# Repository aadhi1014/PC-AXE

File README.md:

# PC-AXE: PCIe-Based Bitcoin Miner (12x BM1370, 14.4TH/s @ 200W)

**PC-AXE** is a compact, PCIe x4-based, open-hardware Bitcoin miner designed to plug directly into desktop computers. Inspired by [Bitaxe](https://github.com/skot/bitaxe), Bitcrane, and professional mining cards, PC-AXE uses twelve BM1370 ASIC chips and a 6-phase high-efficiency buck converter to deliver up to **14.4TH/s** of hashrate at just **200W** power draw.

**Note:** PC-AXE is a **work in progress**. Hardware files are being finalized, and firmware development is ongoing. Community contributions and testing feedback are welcome.

---

*Top side of the PC-AXE board*

*Bottom side of the PC-AXE board*

---

## Features

- **Standard PCIe x4 Form Factor**
  - Easily integrates into modern desktop systems
  - Powered via PCIe slot with external power input

- **12 × BM1370 ASIC Chips**
  - Same chips used in Antminer S21
  - Estimated hashrate of ~1.2TH/s per chip

- **6-Phase 180A Buck Converter**
  - High-efficiency power delivery at 1.1V
  - Total power consumption approximately 200W

- **Fully Open-Source Design**
  - Includes KiCad schematics, layout, and source files
  - Planned firmware compatibility with Bitaxe ecosystem

- **UART Debug Interface**
  - Communicates via USB-to-UART bridge (e.g. FT4232H)
  - Supports daisy-chained UART control for ASICs

- **Design Inspiration**
  - Derived from Bitaxe (compact solo miner)
  - Influenced by Bitcrane

---

## Getting Started

### Build Instructions

1. Open the project in KiCad 7 or newer
2. Review the schematic and PCB layout
3. Export Gerber files and order the PCB from your preferred manufacturer
4. Assemble the board using the BOM (to be published)
5. Flash control firmware (currently in development)

### UART Connection

Connect an FTDI FT4232H or equivalent USB-to-UART adapter to the debug header. A single UART channel can control all 12 ASICs.

---

## Important License Notice  
This project was relicensed under the **TAPR Open Hardware License – Non-Commercial (OHL-NC)** on **July 11, 2025**.  
All clones and forks made **after this date** are subject to **non-commercial use only**.  

**Commercial use, manufacturing, or distribution of this work is strictly prohibited without explicit written permission from the copyright holder.**  

If you cloned this repository *before July 11, 2025*, please contact the author for updated licensing terms.

---

## License

This hardware design is licensed under the TAPR Open Hardware License – Non-Commercial (OHL-NC).  
You are free to use, modify, and distribute for **non-commercial purposes**.  

**Commercial use requires explicit written permission from the copyright holder.**  
See the [LICENSE](LICENSE) file for details.

---

## Acknowledgments

This project draws inspiration and technical insight from several open-source mining hardware efforts:

- [Bitaxe](https://github.com/skot/bitaxe) – foundational open hardware Bitcoin miner  
- [NerdAxe](https://github.com/BitMaker-hub/NerdAxe) – compact ESP32-based BM1370 miner 
- [NerdOCTAXE-Gamma](https://github.com/5toliv/NerdOCTAXE-Gamma) – 8‑ASIC miner derived from NerdQaxe 
- [NerdEKO‑Gamma](https://github.com/phil31/NerdEKO-Gamma) – ESP32-based miner reference design   
- [Bitcrane](https://bitcointalk.org/index.php?topic=951507.0) – USB antminer control board  design

We thank these creators for their contributions to the open-source mining community.
---

## Contact / Collaboration

If you are a developer, hardware enthusiast, or miner interested in contributing to this open hardware project, feel free to open issues or pull requests. Community collaboration is welcome.

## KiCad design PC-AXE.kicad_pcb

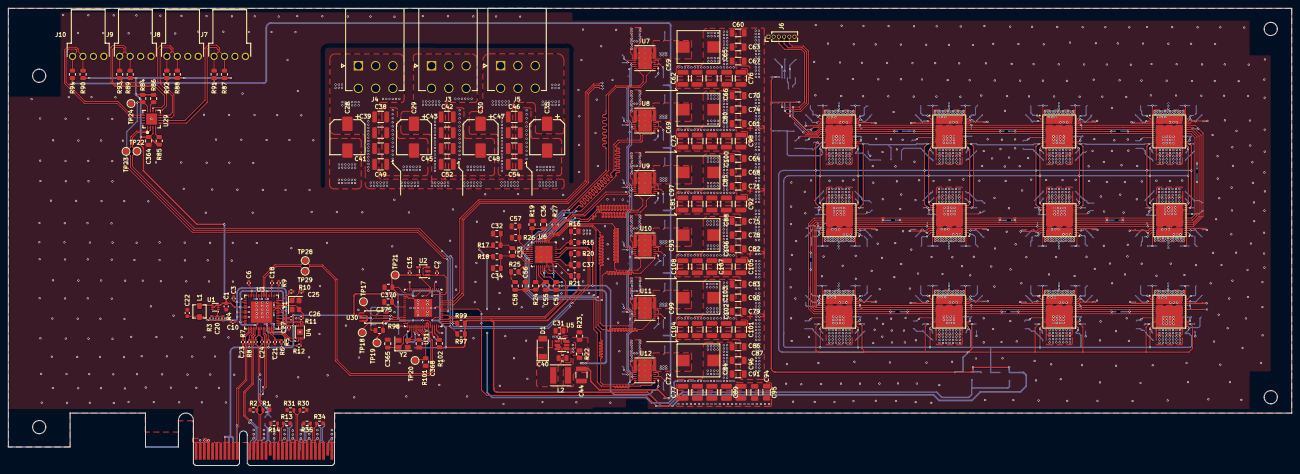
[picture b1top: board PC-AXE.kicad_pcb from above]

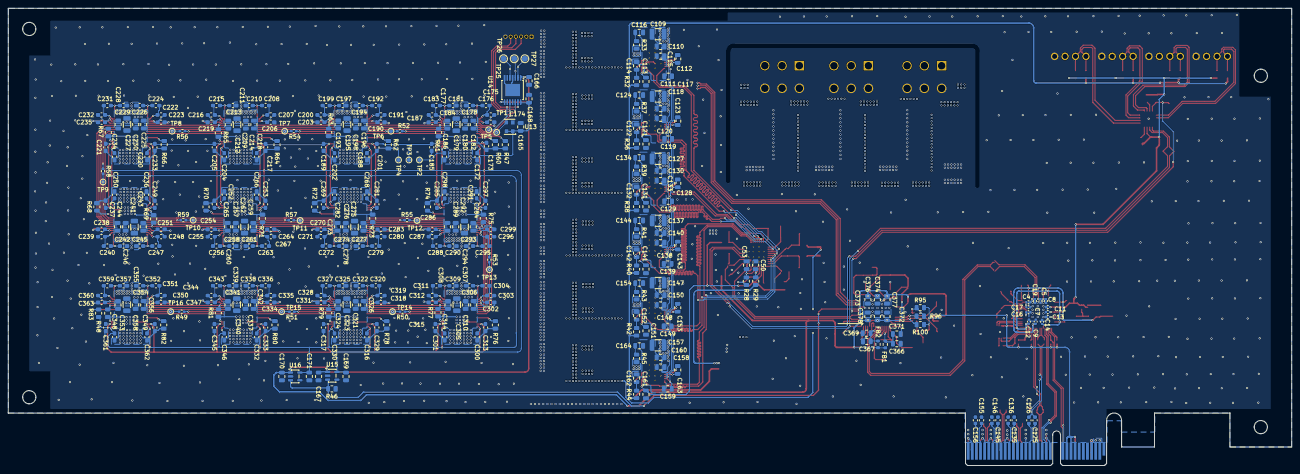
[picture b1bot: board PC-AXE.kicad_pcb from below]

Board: 6 copper layers, 312.0 x 111.2 mm, 565 parts (359 on the bottom side), 297 nets.

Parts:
C1: 10uF; C_0603_1608Metric
C2, C15: 10uF; C_0402_1005Metric
C3, C4, C5, C6, C7, C8, C9, C10, C11, C12, C13, C14, C16, C17, C18, C19, C23, C24, C27: 100nF; C_0402_1005Metric
C20: 10pF; C_0402_1005Metric
C21: 1uF; C_0402_1005Metric
C22: 22uF; C_0603_1608Metric
C25, C26: 18pF; C_0402_1005Metric
C28, C29, C30, C35: 470µ/25V; CP_Elec_8x10
C31, C177, C193, C209, C225, C241, C257, C273, C289, C305, C321, C337, C353: 10µF/25V; C_0805_2012Metric
C32, C34: 22pF; C_0805_2012Metric
C33: 100pF; C_0805_2012Metric
C36, C37, C58, C111, C116, C119, C124, C129, C134, C139, C144, C149, C154, C159, C164: 1nF; C_0805_2012Metric
C38, C39, C41, C42, C43, C44, C45, C46, C47, C48, C49, C52, C54, C109, C117, C127, C137, C147, C157: 22µ/25V; C_1210_3225Metric
C40: 10nF; C_0805_2012Metric
C50: 4.7µF/16V; C_0805_2012Metric
C51, C53, C110, C118, C128, C138, C148, C158, C169, C171, C180, C196, C212, C228, C244, C260, C276, C292, C308, C324, C340, C356: 1µF/25V; C_0805_2012Metric
C55: 330nF; C_0805_2012Metric
C56: 12pF; C_0805_2012Metric
C57: 2.2nF; C_0805_2012Metric
C59, C62, C65, C66, C69, C72, C73, C76, C77, C80, C81, C84, C85, C88, C89, C92, C93, C96, C97, C98, C99, C100, C101, C102, C103, C104, C105, C106, C107, C108: 330µF/4V; C_1210_3225Metric
C60, C61, C63, C64, C67, C68, C70, C71, C74, C75, C78, C79, C82, C83, C86, C87, C90, C91, C94, C95, C179, C195, C211, C227, C243, C259, C275, C291, C307, C323, C339, C355: 100µ/6.3V; C_1206_3216Metric
C112, C113, C115, C120, C121, C123, C130, C131, C133, C140, C141, C143, C150, C151, C153, C160, C161, C163, C165, C166, C167, C168, C170, C182, C198, C214, C230, C246, C262, C278, C294, C310, C326, C342, C358: 100nF; C_0805_2012Metric
C114, C122, C132, C142, C152, C162: 2.2µF/16V; C_0805_2012Metric
C125, C126, C135, C136, C145, C146, C155, C156: 100n; C_0603_1608Metric
C172, C173, C174, C175, C176, C178, C181, C183, C184, C185, C186, C187, C188, C189, C190, C191, C192, C194, C197, C199, C200, C201, C202, C203, C204, C205, C206, C207, C208, C210, C213, C215, C216, C217, C218, C219, C220, C221, C222, C223, C224, C226, C229, C231, C232, C233, C234, C235, C236, C237, C238, C239, C240, C242, C245, C247, C248, C249, C250, C251, C252, C253, C254, C255, C256, C258, C261, C263, C264, C265, C266, C267, C268, C269, C270, C271, C272, C274, C277, C279, C280, C281, C282, C283, C284, C285, C286, C287, C288, C290, C293, C295, C296, C297, C298, C299, C300, C301, C302, C303, C304, C306, C309, C311, C312, C313, C314, C315, C316, C317, C318, C319, C320, C322, C325, C327, C328, C329, C330, C331, C332, C333, C334, C335, C336, C338, C341, C343, C344, C345, C346, C347, C348, C349, C350, C351, C352, C354, C357, C359, C360, C361, C362, C363: 1µF/6.3V; C_0603_1608Metric_Pad1.08x0.95mm_HandSolder
C364, C369, C371, C372, C373, C374, C375, C376, C377, C378: 0.1uF; C_0805_2012Metric
C365, C368: 27pf; C_0805_2012Metric
C366, C367: 4.7uF; C_0805_2012Metric
C370: 3.3uF; C_0805_2012Metric
D1: PMEG4030EP,115; D_SOD-128
FB1, FB2: FerriteBead_Small; R_0603_1608Metric
J1: PCIexpress_bracket; PCIexpress_bracket_full
J2: PCIexpress_x4
J3, J4, J5: 353180620; MOLEX_353180620
J6: Conn_01x06; PinHeader_1x06_P1.27mm_Vertical
J7, J8, J9, J10: 61900411021; CONN-TH_4P-P2.54_HCTL_HC-2510-4AW
L1: 1uH; L_Vishay_IHLP-1212
L2: 4.7µH; L_Taiyo-Yuden_NR-50xx
L3, L4, L5, L6, L7, L8: 220nH; IFLR-4031GC-01-8x10
NT1, NT2: NetTie_2; NetTie-2_SMD_Pad0.5mm
R1, R2, R13, R14, R30, R31, R34, R35: 49.9; R_0603_1608Metric
R3: 75K; R_0402_1005Metric
R4: 100K; R_0402_1005Metric
R5, R6, R8, R12: 10K; R_0402_1005Metric
R7: DNP; R_0402_1005Metric
R9: 4.7K; R_0402_1005Metric
R10: 6.04K; R_0402_1005Metric
R11: 15K; R_0402_1005Metric
R15, R23: 16.5K; R_0805_2012Metric
R16: 24.3K; R_0805_2012Metric
R17, R18: 51 0.5%; R_0805_2012Metric
R19: 121K; R_0805_2012Metric
R20, R21, R46, R47, R48: 10K; R_0805_2012Metric
R22: 86.6K; R_0805_2012Metric
R24: 2.55K; R_0805_2012Metric
R25: 8.06K; R_0805_2012Metric
R26: 33.2K; R_0805_2012Metric
R27: 100K; R_0805_2012Metric
R28, R29: 2.2R; R_0805_2012Metric
R32, R33, R36, R37, R38, R39, R40, R41, R42, R43, R44, R45: 1R; R_0805_2012Metric
R49, R50, R51, R52, R53, R54, R55, R56, R57, R58, R59: 33R; R_0402_1005Metric_Pad0.72x0.64mm_HandSolder
R60, R62, R64, R66, R68, R70, R72, R74, R76, R78, R80, R82: 1K; R_0805_2012Metric
R61, R63, R65, R67, R69, R71, R73, R75, R77, R79, R81, R83: 2K; R_0805_2012Metric
R84, R97, R99: 4.7k; R_0805_2012Metric
R85: 33k; R_0805_2012Metric
R86: 22k; R_0805_2012Metric
R87, R88, R89, R90: 36k; R_0805_2012Metric
R91, R92, R93, R94, R95, R98, R100: 10k; R_0805_2012Metric
R96: 2.2k; R_0805_2012Metric
R101: 12k; R_0805_2012Metric
R102: 1k; R_0805_2012Metric
TP1, TP2, TP3, TP4, TP5, TP6, TP7, TP8, TP9, TP10, TP11, TP12, TP13, TP14, TP15, TP16: TestPoint; TestPoint_Pad_D1.0mm
TP17, TP18, TP19, TP20, TP21, TP22, TP23, TP24, TP25, TP26, TP27, TP28, TP29: TestPoint; TestPoint_Pad_D1.5mm
U1: TLV62568ADRLR; SOT-563
U2: AP2204K-1.8; SOT-23-5
U3: VL805; QFN-68-1EP_8x8mm_P0.4mm_EP5.2x5.2mm
U4: W25Q32JVZP; DFN-8-1EP_3x2mm_P0.5mm_EP1.36x1.46mm
U5: AP3211; SOT-23-6
U6: TPS53667RTAR; IC_TPS53667RTAR
U7, U8, U9, U10, U11, U12: CSD95472Q5MC; IC_CSD95490Q5MC
U13: 25MHz; Oscillator_SMD_EuroQuartz_XO32-4Pin_3.2x2.5mm
U14: TXU0304PW; TSSOP-14-1EP_4.4x5mm_P0.65mm
U15: MCP1824T-0802E; SOT-23-5
U16: MCP1824T-1202E; SOT-23-5
U17, U18, U19, U20, U21, U22, U23, U24, U25, U26, U27, U28: BM1370_mode1; BM1370
U29: EMC2305; QFN16_4x4MC_MCH
U30: M93C46-WDW6TP; TSSOP-8_L4.4-W3.0-P0.65-LS6.4-BL
U31: FT4232HQ; QFN50P900X900X105-65N
Y1: 25Mhz; Crystal_SMD_3225-4Pin_3.2x2.5mm
Y2: 12MHz; Crystal_SMD_3225-4Pin_3.2x2.5mm

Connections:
+0V8: C169.1, C173.2, C185.2, C189.2, C201.2, C205.2, C217.2, C221.2, C233.2, C237.2, C249.2, C253.2, C265.2, C269.2, C281.2, C285.2, C297.2, C301.2, C313.2, C317.2, C329.2, C333.2, C345.2, C349.2, C361.2, TP3.1, U15.5 (VOUT), U17.14 (VDDIO_08_0), U17.17 (VDDIO_08_1), U18.14 (VDDIO_08_0), U18.17 (VDDIO_08_1), U19.14 (VDDIO_08_0), U19.17 (VDDIO_08_1), U20.14 (VDDIO_08_0), U20.17 (VDDIO_08_1), U21.14 (VDDIO_08_0), U21.17 (VDDIO_08_1), U22.14 (VDDIO_08_0), U22.17 (VDDIO_08_1), U23.14 (VDDIO_08_0), U23.17 (VDDIO_08_1), U24.14 (VDDIO_08_0), U24.17 (VDDIO_08_1), U25.14 (VDDIO_08_0), U25.17 (VDDIO_08_1), U26.14 (VDDIO_08_0), U26.17 (VDDIO_08_1), U27.14 (VDDIO_08_0), U27.17 (VDDIO_08_1), U28.14 (VDDIO_08_0), U28.17 (VDDIO_08_1)
+1V1: C3.2, C5.2, C7.2, C9.2, C11.2, C13.2, C16.2, C18.2, C20.1, C22.1, L1.2, R3.1, U3.3 (VCCA10SSRX34), U3.9 (VDD), U3.12 (VCCA10SSRX34), U3.29 (VDD), U3.45 (VDD), U3.54 (VCCA10SSRX12), U3.60 (VDD), U3.63 (VCCA10SSRX12)
+1V2: C165.1, C168.1, C171.1, C172.1, C186.1, C188.1, C202.1, C204.1, C218.1, C220.1, C234.1, C236.1, C250.1, C252.1, C266.1, C268.1, C282.1, C284.1, C298.1, C300.1, C314.1, C316.1, C330.1, C332.1, C346.1, C348.1, C362.1, R48.2, TP2.1, U13.1 (Standby), U13.4 (VDD), U14.14 (VCCB), U16.5 (VOUT), U17.15 (VDDIO_12_0), U17.16 (VDDIO_12_1), U18.15 (VDDIO_12_0), U18.16 (VDDIO_12_1), U19.15 (VDDIO_12_0), U19.16 (VDDIO_12_1), U20.15 (VDDIO_12_0), U20.16 (VDDIO_12_1), U21.15 (VDDIO_12_0), U21.16 (VDDIO_12_1), U22.15 (VDDIO_12_0), U22.16 (VDDIO_12_1), U23.15 (VDDIO_12_0), U23.16 (VDDIO_12_1), U24.15 (VDDIO_12_0), U24.16 (VDDIO_12_1), U25.15 (VDDIO_12_0), U25.16 (VDDIO_12_1), U26.15 (VDDIO_12_0), U26.16 (VDDIO_12_1), U27.15 (VDDIO_12_0), U27.16 (VDDIO_12_1), U28.15 (VDDIO_12_0), U28.16 (VDDIO_12_1)
+1V8: C15.1, C370.1, C372.1, C373.1, C374.1, TP21.1, U2.5 (VOUT), U31.12 (VCORE), U31.37 (VCORE), U31.49 (VREGOUT), U31.64 (VCORE)
+3V3: C1.2, C2.1, C4.2, C6.2, C8.2, C10.2, C12.2, C14.2, C17.2, C19.2, C27.2, C166.1, C167.1, C170.1, C364.1, C375.1, C376.1, C377.1, C378.1, FB1.1, FB2.1, J2.A9 (+3.3V), J2.A10 (+3.3V), J2.B8 (+3.3V), R5.2, R6.2, R7.2, R8.2, R11.2, R12.1, R21.1, R84.2, R85.2, R86.2, R87.1, R88.1, R89.1, R90.1, R95.2, R97.2, R98.2, R99.2, R100.2, R102.1, U1.3 (VIN), U1.5 (EN), U2.1 (VIN), U2.3 (EN), U3.6 (VCCA33SS34), U3.15 (VCCA33SS34), U3.23 (VCCA33PEX), U3.32 (VSUS33), U3.46 (VSUS33), U3.49 (VCCA33SSM), U3.57 (VCCA33SS12), U3.66 (VCCA33SS12), U4.7 (IO3), U4.8 (VCC), U14.1 (VCCA), U14.8 (OE), U15.1 (VIN), U16.1 (VIN), U29.3 (VDD), U30.6 (ORG), U30.8 (VCC), U31.20 (VCCIO), U31.31 (VCCIO), U31.42 (VCCIO), U31.50 (VREGIN), U31.56 (VCCIO)
+5V_STDBY: C44.1, L2.2, R22.1, R29.1, R32.1, R36.1, R38.1, R40.1, R42.1, R44.1, R91.2, R92.2, R93.2, R94.2
+12V: C28.1, C29.1, C30.1, C31.1, C35.1, C38.1, C39.1, C41.1, C42.1, C43.1, C45.1, C46.1, C47.1, C48.1, C49.1, C52.1, C54.1, C109.1, C110.1, C112.1, C117.1, C118.1, C120.1, C127.1, C128.1, C130.1, C137.1, C138.1, C140.1, C147.1, C148.1, C150.1, C157.1, C158.1, C160.1, J2.A2 (+12V), J2.A3 (+12V), J2.B1 (+12V), J2.B2 (+12V), J2.B3 (+12V), J3.1, J3.2, J3.3, J4.1, J4.2, J4.3, J5.1, J5.2, J5.3, J7.2, J8.2, J9.2, J10.2, R28.1, U5.4 (EN), U5.5 (IN), U7.7 (VIN), U8.7 (VIN), U9.7 (VIN), U10.7 (VIN), U11.7 (VIN), U12.7 (VIN)
+VREF: C55.1, C56.2, C58.2, C113.1, C121.1, C131.1, C141.1, C151.1, C161.1, R15.2, R24.2, U6.13 (VREF), U7.2 (REFIN), U8.2 (REFIN), U9.2 (REFIN), U10.2 (REFIN), U11.2 (REFIN), U12.2 (REFIN)
/BM1370_chain/BM1370-1/BI: R47.2, U17.9 (BI)
/BM1370_chain/BM1370-1/BO: U17.22 (BO), U18.9 (BI)
/BM1370_chain/BM1370-1/CLKI: TP5.1, U13.3 (Out), U17.8 (CLKI)
/BM1370_chain/BM1370-1/CLKO: R52.1, U17.23 (CLKO)
/BM1370_chain/BM1370-1/CO: U17.25 (CO), U18.6 (CI)
/BM1370_chain/BM1370-1/NRSTO: R61.2, U17.26 (NRSTO), U18.5 (NRSTI)
/BM1370_chain/BM1370-1/RI: U17.24 (RI), U18.7 (RO)
/BM1370_chain/BM1370-2/BO: U18.22 (BO), U19.9 (BI)
/BM1370_chain/BM1370-2/CLKI: R52.2, TP6.1, U18.8 (CLKI)
/BM1370_chain/BM1370-2/CLKO: R54.1, U18.23 (CLKO)
/BM1370_chain/BM1370-2/CO: U18.25 (CO), U19.6 (CI)
/BM1370_chain/BM1370-2/NRSTO: R63.2, U18.26 (NRSTO), U19.5 (NRSTI)
/BM1370_chain/BM1370-2/RI: U18.24 (RI), U19.7 (RO)
/BM1370_chain/BM1370-3/BO: U19.22 (BO), U20.9 (BI)
/BM1370_chain/BM1370-3/CLKI: R54.2, TP7.1, U19.8 (CLKI)
/BM1370_chain/BM1370-3/CLKO: R56.1, U19.23 (CLKO)
/BM1370_chain/BM1370-3/CO: U19.25 (CO), U20.6 (CI)
/BM1370_chain/BM1370-3/NRSTO: R65.2, U19.26 (NRSTO), U20.5 (NRSTI)
/BM1370_chain/BM1370-3/RI: U19.24 (RI), U20.7 (RO)
/BM1370_chain/BM1370-4/BO: U20.22 (BO), U21.9 (BI)
/BM1370_chain/BM1370-4/CLKI: R56.2, TP8.1, U20.8 (CLKI)
/BM1370_chain/BM1370-4/CLKO: R58.1, U20.23 (CLKO)
/BM1370_chain/BM1370-4/CO: U20.25 (CO), U21.6 (CI)
/BM1370_chain/BM1370-4/NRSTO: R67.2, U20.26 (NRSTO), U21.5 (NRSTI)
/BM1370_chain/BM1370-4/RI: U20.24 (RI), U21.7 (RO)
/BM1370_chain/BM1370-5/BO: U21.22 (BO), U22.9 (BI)
/BM1370_chain/BM1370-5/CLKI: R58.2, TP9.1, U21.8 (CLKI)
/BM1370_chain/BM1370-5/CLKO: R59.1, U21.23 (CLKO)
/BM1370_chain/BM1370-5/CO: U21.25 (CO), U22.6 (CI)
/BM1370_chain/BM1370-5/NRSTO: R69.2, U21.26 (NRSTO), U22.5 (NRSTI)
/BM1370_chain/BM1370-5/RI: U21.24 (RI), U22.7 (RO)
/BM1370_chain/BM1370-6/BO: U22.22 (BO), U23.9 (BI)
/BM1370_chain/BM1370-6/CLKI: R59.2, TP10.1, U22.8 (CLKI)
/BM1370_chain/BM1370-6/CLKO: R57.1, U22.23 (CLKO)
/BM1370_chain/BM1370-6/CO: U22.25 (CO), U23.6 (CI)
/BM1370_chain/BM1370-6/NRSTO: R71.2, U22.26 (NRSTO), U23.5 (NRSTI)
/BM1370_chain/BM1370-6/RI: U22.24 (RI), U23.7 (RO)
/BM1370_chain/BM1370-7/BO: U23.22 (BO), U24.9 (BI)
/BM1370_chain/BM1370-7/CLKI: R57.2, TP11.1, U23.8 (CLKI)
/BM1370_chain/BM1370-7/CLKO: R55.1, U23.23 (CLKO)
/BM1370_chain/BM1370-7/CO: U23.25 (CO), U24.6 (CI)
/BM1370_chain/BM1370-7/NRSTO: R73.2, U23.26 (NRSTO), U24.5 (NRSTI)
/BM1370_chain/BM1370-7/RI: U23.24 (RI), U24.7 (RO)
/BM1370_chain/BM1370-8/BO: U24.22 (BO), U25.9 (BI)
/BM1370_chain/BM1370-8/CLKI: R55.2, TP12.1, U24.8 (CLKI)
/BM1370_chain/BM1370-8/CLKO: R53.1, U24.23 (CLKO)
/BM1370_chain/BM1370-8/CO: U24.25 (CO), U25.6 (CI)
/BM1370_chain/BM1370-8/NRSTO: R75.2, U24.26 (NRSTO), U25.5 (NRSTI)
/BM1370_chain/BM1370-8/RI: U24.24 (RI), U25.7 (RO)
/BM1370_chain/BM1370-9/CLKI: R53.2, TP13.1, U25.8 (CLKI)
/BM1370_chain/BM1370-9/CLKO: R50.1, U25.23 (CLKO)
/BM1370_chain/BM1370-10/BI: U25.22 (BO), U26.9 (BI)
/BM1370_chain/BM1370-10/BO: U26.22 (BO), U27.9 (BI)
/BM1370_chain/BM1370-10/CI: U25.25 (CO), U26.6 (CI)
/BM1370_chain/BM1370-10/CLKI: R50.2, TP14.1, U26.8 (CLKI)
/BM1370_chain/BM1370-10/CLKO: R51.1, U26.23 (CLKO)
/BM1370_chain/BM1370-10/CO: U26.25 (CO), U27.6 (CI)
/BM1370_chain/BM1370-10/NRSTI: R77.2, U25.26 (NRSTO), U26.5 (NRSTI)
/BM1370_chain/BM1370-10/NRSTO: R79.2, U26.26 (NRSTO), U27.5 (NRSTI)
/BM1370_chain/BM1370-10/RI: U26.24 (RI), U27.7 (RO)
/BM1370_chain/BM1370-10/RO: U25.24 (RI), U26.7 (RO)
/BM1370_chain/BM1370-11/BO: U27.22 (BO), U28.9 (BI)
/BM1370_chain/BM1370-11/CLKI: R51.2, TP15.1, U27.8 (CLKI)
/BM1370_chain/BM1370-11/CLKO: R49.1, U27.23 (CLKO)
/BM1370_chain/BM1370-11/CO: U27.25 (CO), U28.6 (CI)
/BM1370_chain/BM1370-11/NRSTO: R81.2, U27.26 (NRSTO), U28.5 (NRSTI)
/BM1370_chain/BM1370-11/RI: U27.24 (RI), U28.7 (RO)
/BM1370_chain/BM1370-12/CLKI: R49.2, TP16.1, U28.8 (CLKI)
/BM1370_chain/BM1370-12/NRSTO: R83.2, U28.26 (NRSTO)
/BM1370_chain/BM1370-12/RI: R48.1, U28.24 (RI)
/BM1370_chain/CI: J6.4, U14.12 (B2Y), U17.6 (CI)
/BM1370_chain/RO: J6.5, U14.10 (B4), U17.7 (RO)
/BM1370_chain/RST_N: J6.3, TP1.1, U14.13 (B1Y), U17.5 (NRSTI)
/DN: TP28.1, U3.59 (USB2D1-), U31.7 (DM)
/DP: TP29.1, U3.58 (USB2D1+), U31.8 (DP)
/FAN/PWM1: J7.4, R91.1, U29.5 (PWM1)
/FAN/PWM2: J8.4, R92.1, U29.7 (PWM2)
/FAN/PWM3: J9.4, R93.1, U29.9 (PWM3)
/FAN/PWM4: J10.4, R94.1, U29.13 (PWM4)
/FAN/TACH1: J7.3, R87.2, U29.6 (TACH1)
/FAN/TACH2: J8.3, R88.2, U29.8 (TACH2)
/FAN/TACH3: J9.3, R89.2, U29.10 (TACH3)
/FAN/TACH4: J10.3, R90.2, U29.14 (TACH4)
/FAN_ALERT: R84.1, TP24.1, U29.12 (~ALERT), U31.23 (ADBUS6)
/LDO_EN: R46.1, U15.3 (EN), U16.3 (EN), U31.24 (ADBUS7)
/PCIexpress_connector/_PER0_N: C126.1, J2.A17 (PERn0)
/PCIexpress_connector/_PER0_P: C125.2, J2.A16 (PERp0)
/PCIexpress_connector/_PER1_N: C136.1, J2.A22 (PERn1)
/PCIexpress_connector/_PER1_P: C135.2, J2.A21 (PERp1)
/PCIexpress_connector/_PER2_N: C146.1, J2.A26 (PERn2)
/PCIexpress_connector/_PER2_P: C145.2, J2.A25 (PERp2)
/PCIexpress_connector/_PER3_N: C156.1, J2.A30 (PERn3)
/PCIexpress_connector/_PER3_P: C155.2, J2.A29 (PERp3)
/PER0_N: C23.1, C126.2
/PER0_P: C24.1, C125.1
/PET0_N: J2.B15 (PETn0), R1.1, U3.27 (PE_RXP)
/PET0_P: J2.B14 (PETp0), R2.1, U3.28 (PE_RXN)
/PET1_N: J2.B20 (PETn1), R13.1
/PET1_P: J2.B19 (PETp1), R14.1
/PET2_N: J2.B24 (PETn2), R30.1
/PET2_P: J2.B23 (PETp2), R31.1
/PET3_N: J2.B28 (PETn3), R34.1
/PET3_P: J2.B27 (PETp3), R35.1
/POWER/FCCM: R27.2, U6.39 (~SKIP-NVM), U7.10 (FCCM), U8.10 (FCCM), U9.10 (FCCM), U10.10 (FCCM), U11.10 (FCCM), U12.10 (FCCM)
/POWER/TPS_CSP1: U6.3 (CSP1), U9.1 (IOUT)
/POWER/TPS_CSP2: U6.4 (CSP2), U7.1 (IOUT)
/POWER/TPS_CSP3: U6.5 (CSP3), U8.1 (IOUT)
/POWER/TPS_CSP4: U6.6 (CSP4), U10.1 (IOUT)
/POWER/TPS_CSP5: U6.7 (CSP5), U11.1 (IOUT)
/POWER/TPS_CSP6: U6.8 (CSP6), U12.1 (IOUT)
/POWER/TPS_PWM1: U6.38 (PWM1), U9.12 (PWM)
/POWER/TPS_PWM2: U6.37 (PWM2), U7.12 (PWM)
/POWER/TPS_PWM3: U6.36 (PWM3), U8.12 (PWM)
/POWER/TPS_PWM4: U6.35 (PWM4), U10.12 (PWM)
/POWER/TPS_PWM5: U6.34 (PWM5), U11.12 (PWM)
/POWER/TPS_PWM6: U6.33 (PWM6), U12.12 (PWM)
/POWER/TSEN: C36.1, C111.1, C119.1, C129.1, C139.1, C149.1, C159.1, R19.2, U6.40 (TSEN), U7.11 (TAO/FAULT), U8.11 (TAO/FAULT), U9.11 (TAO/FAULT), U10.11 (TAO/FAULT), U11.11 (TAO/FAULT), U12.11 (TAO/FAULT)
/POWER/VSENSE+: NT1.2, R17.1
/POWER/VSENSE-: NT2.2, R18.1
/POWER//RESET: R21.2, U6.21 (~RESET)
/REFCLK+: J2.A13 (REFCLK+), U3.21 (PE_CLKP)
/REFCLK-: J2.A14 (REFCLK-), U3.22 (PE_CLKN)
/RESET_N: TP27.1, U14.2 (A1), U31.28 (BDBUS2)
/RXD: TP26.1, U14.5 (A4Y), U31.27 (BDBUS1)
/SCL: R97.1, TP22.1, U6.24 (PMB_CLK), U29.2 (SMCLK), U31.16 (ADBUS0)
/SDA: R99.1, TP23.1, U6.26 (PMB_DIO), U29.1 (SMDATA), U31.17 (ADBUS1), U31.18 (ADBUS2)
/TXD: TP25.1, U14.3 (A2), U31.26 (BDBUS0)
/USB/PCIe_CLK_REQ: R6.1, U3.30 (~PE_CLKREQ)
/USB/SMI: R7.1, U3.18 (~SMI)
/VR_ENABLE: C37.1, R20.1, U6.23 (ENABLE), U31.19 (ADBUS3)
/VR_READY: U6.18 (VR_RDY), U31.21 (ADBUS4)
/~PERST: J2.A11 (~PERST), U3.19 (~PE_RST)
/~WAKE: J2.B11 (~WAKE), R8.1, U3.20 (~PE_WAKE)
GND: C1.1, C2.2, C3.1, C4.1, C5.1, C6.1, C7.1, C8.1, C9.1, C10.1, C11.1, C12.1, C13.1, C14.1, C15.2, C16.1, C17.1, C18.1, C19.1, C21.1, C22.2, C25.1, C26.1, C27.1, C28.2, C29.2, C30.2, C31.2, C32.1, C34.2, C35.2, C36.2, C37.2, C38.2, C39.2, C41.2, C42.2, C43.2, C44.2, C45.2, C46.2, C47.2, C48.2, C49.2, C50.1, C51.2, C52.2, C53.1, C54.2, C55.2, C57.2, C59.2, C60.2, C61.2, C62.2, C63.2, C64.2, C65.2, C66.2, C67.2, C68.2, C69.2, C70.2, C71.2, C72.2, C73.2, C74.2, C75.2, C76.2, C77.2, C78.2, C79.2, C80.2, C81.2, C82.2, C83.2, C84.2, C85.2, C86.2, C87.2, C88.2, C89.2, C90.2, C91.2, C92.2, C93.2, C94.2, C95.2, C96.2, C97.2, C98.2, C99.2, C100.2, C101.2, C102.2, C103.2, C104.2, C105.2, C106.2, C107.2, C108.2, C109.2, C110.2, C111.2, C112.2, C113.2, C114.2, C116.2, C117.2, C118.2, C119.2, C120.2, C121.2, C122.2, C124.2, C127.2, C128.2, C129.2, C130.2, C131.2, C132.2, C134.2, C137.2, C138.2, C139.2, C140.2, C141.2, C142.2, C144.2, C147.2, C148.2, C149.2, C150.2, C151.2, C152.2, C154.2, C157.2, C158.2, C159.2, C160.2, C161.2, C162.2, C164.2, C165.2, C166.2, C167.2, C168.2, C169.2, C170.2, C171.2, C172.2, C173.1, C174.1, C177.2, C179.2, C180.2, C182.2, C185.1, C186.2, C187.2, C188.2, C189.1, C190.1, C193.2, C195.2, C196.2, C198.2, C201.1, C202.2, C203.2, C204.2, C205.1, C206.1, C209.2, C211.2, C212.2, C214.2, C217.1, C218.2, C219.2, C220.2, C221.1, C222.1, C225.2, C227.2, C228.2, C230.2, C233.1, C234.2, C235.2, C236.2, C237.1, C238.1, C241.2, C243.2, C244.2, C246.2, C249.1, C250.2, C251.2, C252.2, C253.1, C254.1, C257.2, C259.2, C260.2, C262.2, C265.1, C266.2, C267.2, C268.2, C269.1, C270.1, C273.2, C275.2, C276.2, C278.2, C281.1, C282.2, C283.2, C284.2, C285.1, C286.1, C289.2, C291.2, C292.2, C294.2, C297.1, C298.2, C299.2, C300.2, C301.1, C302.1, C305.2, C307.2, C308.2, C310.2, C313.1, C314.2, C315.2, C316.2, C317.1, C318.1, C321.2, C323.2, C324.2, C326.2, C329.1, C330.2, C331.2, C332.2, C333.1, C334.1, C337.2, C339.2, C340.2, C342.2, C345.1, C346.2, C347.2, C348.2, C349.1, C350.1, C353.2, C355.2, C356.2, C358.2, C361.1, C362.2, C363.2, C364.2, C365.2, C366.2, C367.2, C368.2, C369.2, C370.2, C371.2, C372.2, C373.2, C374.2, C375.2, C376.2, C377.2, C378.2, D1.2 (A), J2.A4 (GND), J2.A12 (GND), J2.A15 (GND), J2.A18 (GND), J2.A20 (GND), J2.A23 (GND), J2.A24 (GND), J2.A27 (GND), J2.A28 (GND), J2.A31 (GND), J2.B4 (GND), J2.B7 (GND), J2.B13 (GND), J2.B16 (GND), J2.B18 (GND), J2.B21 (GND), J2.B22 (GND), J2.B25 (GND), J2.B26 (GND), J2.B29 (GND), J2.B32 (GND), J3.4, J3.5, J3.6, J4.4, J4.5, J4.6, J5.4, J5.5, J5.6, J6.6, J7.1, J8.1, J9.1, J10.1, NT2.1, R1.2, R2.2, R4.2, R9.1, R10.1, R13.2, R14.2, R16.1, R19.1, R20.2, R23.2, R26.1, R27.1, R30.2, R31.2, R34.2, R35.2, R46.2, R47.1, R60.2, R61.1, R62.2, R63.1, R64.2, R65.1, R66.2, R67.1, R68.2, R69.1, R70.2, R71.1, R72.2, R73.1, R74.2, R75.1, R76.2, R77.1, R78.2, R79.1, R80.2, R81.1, R82.2, R83.1, R101.1, TP4.1, U1.2 (GND), U2.2 (GND), U3.69 (GND), U4.4 (GND), U4.9 (EP), U5.2 (GND), U6.17 (GND_17), U6.20 (GND_20), U6.22 (GND_22), U6.41 (EXP), U7.4 (PGND), U7.13 (PGND), U8.4 (PGND), U8.13 (PGND), U9.4 (PGND), U9.13 (PGND), U10.4 (PGND), U10.13 (PGND), U11.4 (PGND), U11.13 (PGND), U12.4 (PGND), U12.13 (PGND), U13.2 (GND), U14.4 (A3), U14.7 (GND), U14.15 (GND), U15.2 (GND), U16.2 (GND), U17.4 (VSS), U17.13 (PLL_VSS), U17.18 (VSS), U17.27 (VSS), U17.32 (VSS), U18.4 (VSS), U18.13 (PLL_VSS), U18.18 (VSS), U18.27 (VSS), U18.32 (VSS), U19.4 (VSS), U19.13 (PLL_VSS), U19.18 (VSS), U19.27 (VSS), U19.32 (VSS), U20.4 (VSS), U20.13 (PLL_VSS), U20.18 (VSS), U20.27 (VSS), U20.32 (VSS), U21.4 (VSS), U21.13 (PLL_VSS), U21.18 (VSS), U21.27 (VSS), U21.32 (VSS), U22.4 (VSS), U22.13 (PLL_VSS), U22.18 (VSS), U22.27 (VSS), U22.32 (VSS), U23.4 (VSS), U23.13 (PLL_VSS), U23.18 (VSS), U23.27 (VSS), U23.32 (VSS), U24.4 (VSS), U24.13 (PLL_VSS), U24.18 (VSS), U24.27 (VSS), U24.32 (VSS), U25.4 (VSS), U25.13 (PLL_VSS), U25.18 (VSS), U25.27 (VSS), U25.32 (VSS), U26.4 (VSS), U26.13 (PLL_VSS), U26.18 (VSS), U26.27 (VSS), U26.32 (VSS), U27.4 (VSS), U27.13 (PLL_VSS), U27.18 (VSS), U27.27 (VSS), U27.32 (VSS), U28.4 (VSS), U28.13 (PLL_VSS), U28.18 (VSS), U28.27 (VSS), U28.32 (VSS), U29.17 (GND), U30.5 (VSS), U30.7 (DU), U31.1 (GND), U31.5 (GND), U31.10 (AGND), U31.11 (GND), U31.13 (TEST), U31.15 (GND), U31.25 (GND), U31.35 (GND), U31.47 (GND), U31.51 (GND), U31.65 (EPAD), Y1.2, Y1.4, Y2.2 (GND), Y2.4 (GND__1)
unnamed: C58.1, R25.1
unnamed: C116.1, R33.1
unnamed: C124.1, R37.1
unnamed: C134.1, R39.1
unnamed: C144.1, R41.1
unnamed: C154.1, R43.1
unnamed: C164.1, R45.1
unnamed: C40.2, D1.1 (K), L2.1, U5.6 (SW)
unnamed: C20.2, R3.2, R4.1, U1.1 (FB)
unnamed: L1.1, U1.4 (SW)
unnamed: C24.2, U3.25 (PE_TXN)
unnamed: C23.2, U3.24 (PE_TXP)
unnamed: U3.35 (SPI_CLK), U4.6 (CLK)
unnamed: U3.34 (SPI_CS), U4.1 (~CS)
unnamed: U3.36 (SPI_DI), U4.5 (DI(IO0))
unnamed: U3.33 (SPI_DO), U4.2 (DO(IO1))
unnamed: R10.2, U3.50 (SSREXT)
unnamed: R9.2, U3.51 (TESTEN)
unnamed: C26.2, U3.47 (XI), Y1.3
unnamed: C25.2, U3.48 (XO), Y1.1
unnamed: C21.2, R5.1, U3.31 (~PONRST)
unnamed: R11.1, U3.37 (~USBHOC4), U3.39 (~USBHOC3), U3.41 (~USBHOC2), U3.43 (~USBHOC1)
unnamed: R12.2, U4.3 (IO2)
unnamed: C40.1, U5.1 (BS)
unnamed: R22.2, R23.1, U5.3 (FB)
unnamed: R15.1, R16.2, U6.28 (ADDR-TRISE)
unnamed: C56.1, R25.2, U6.11 (COMP)
unnamed: C57.1, R26.2, U6.2 (IMON)
unnamed: R24.1, U6.12 (ISUM)
unnamed: C51.1, U6.14 (V3R3)
unnamed: C50.2, R29.2, U6.15 (V5)
unnamed: C53.2, R28.2, U6.16 (VIN)
unnamed: C33.2, C34.1, R18.2, U6.10 (VSN)
unnamed: C32.2, C33.1, R17.2, U6.9 (VSP)
unnamed: C115.1, U7.9 (BOOT)
unnamed: C115.2, U7.8 (BOOT_R)
unnamed: C114.1, R32.2, U7.3 (ENABLE), U7.5 (VDD)
unnamed: L3.1, R33.2, U7.6 (VSW)
unnamed: C123.1, U8.9 (BOOT)
unnamed: C123.2, U8.8 (BOOT_R)
unnamed: C122.1, R36.2, U8.3 (ENABLE), U8.5 (VDD)
unnamed: L4.1, R37.2, U8.6 (VSW)
unnamed: C133.1, U9.9 (BOOT)
unnamed: C133.2, U9.8 (BOOT_R)
unnamed: C132.1, R38.2, U9.3 (ENABLE), U9.5 (VDD)
unnamed: L5.1, R39.2, U9.6 (VSW)
unnamed: C143.1, U10.9 (BOOT)
unnamed: C143.2, U10.8 (BOOT_R)
unnamed: C142.1, R40.2, U10.3 (ENABLE), U10.5 (VDD)
unnamed: L6.1, R41.2, U10.6 (VSW)
unnamed: C153.1, U11.9 (BOOT)
unnamed: C153.2, U11.8 (BOOT_R)
unnamed: C152.1, R42.2, U11.3 (ENABLE), U11.5 (VDD)
unnamed: L7.1, R43.2, U11.6 (VSW)
unnamed: C163.1, U12.9 (BOOT)
unnamed: C163.2, U12.8 (BOOT_R)
unnamed: C162.1, R44.2, U12.3 (ENABLE), U12.5 (VDD)
unnamed: L8.1, R45.2, U12.6 (VSW)
unnamed: R60.1, U17.11 (LITE_PAD)
unnamed: C174.2, C175.1, U17.3 (VDD1_0)
unnamed: C184.2, C187.1, U17.28 (VDD1_1)
unnamed: C175.2, C176.1, U17.2 (VDD2_0)
unnamed: C183.2, C184.1, U17.29 (VDD2_1)
unnamed: C176.2, C178.1, U17.1 (VDD3_0)
unnamed: C181.2, C183.1, U17.30 (VDD3_1)
unnamed: R62.1, U18.11 (LITE_PAD)
unnamed: C190.2, C191.1, U18.3 (VDD1_0)
unnamed: C200.2, C203.1, U18.28 (VDD1_1)
unnamed: C191.2, C192.1, U18.2 (VDD2_0)
unnamed: C199.2, C200.1, U18.29 (VDD2_1)
unnamed: C192.2, C194.1, U18.1 (VDD3_0)
unnamed: C197.2, C199.1, U18.30 (VDD3_1)
unnamed: R64.1, U19.11 (LITE_PAD)
unnamed: C206.2, C207.1, U19.3 (VDD1_0)
unnamed: C216.2, C219.1, U19.28 (VDD1_1)
unnamed: C207.2, C208.1, U19.2 (VDD2_0)
unnamed: C215.2, C216.1, U19.29 (VDD2_1)
unnamed: C208.2, C210.1, U19.1 (VDD3_0)
unnamed: C213.2, C215.1, U19.30 (VDD3_1)
unnamed: R66.1, U20.11 (LITE_PAD)
unnamed: C222.2, C223.1, U20.3 (VDD1_0)
unnamed: C232.2, C235.1, U20.28 (VDD1_1)
unnamed: C223.2, C224.1, U20.2 (VDD2_0)
unnamed: C231.2, C232.1, U20.29 (VDD2_1)
unnamed: C224.2, C226.1, U20.1 (VDD3_0)
unnamed: C229.2, C231.1, U20.30 (VDD3_1)
unnamed: R68.1, U21.11 (LITE_PAD)
unnamed: C238.2, C239.1, U21.3 (VDD1_0)
unnamed: C248.2, C251.1, U21.28 (VDD1_1)
unnamed: C239.2, C240.1, U21.2 (VDD2_0)
unnamed: C247.2, C248.1, U21.29 (VDD2_1)
unnamed: C240.2, C242.1, U21.1 (VDD3_0)
unnamed: C245.2, C247.1, U21.30 (VDD3_1)
unnamed: R70.1, U22.11 (LITE_PAD)
unnamed: C254.2, C255.1, U22.3 (VDD1_0)
unnamed: C264.2, C267.1, U22.28 (VDD1_1)
unnamed: C255.2, C256.1, U22.2 (VDD2_0)
unnamed: C263.2, C264.1, U22.29 (VDD2_1)
unnamed: C256.2, C258.1, U22.1 (VDD3_0)
unnamed: C261.2, C263.1, U22.30 (VDD3_1)
unnamed: R72.1, U23.11 (LITE_PAD)
unnamed: C270.2, C271.1, U23.3 (VDD1_0)
unnamed: C280.2, C283.1, U23.28 (VDD1_1)
unnamed: C271.2, C272.1, U23.2 (VDD2_0)
unnamed: C279.2, C280.1, U23.29 (VDD2_1)
unnamed: C272.2, C274.1, U23.1 (VDD3_0)
unnamed: C277.2, C279.1, U23.30 (VDD3_1)
unnamed: R74.1, U24.11 (LITE_PAD)
unnamed: C286.2, C287.1, U24.3 (VDD1_0)
unnamed: C296.2, C299.1, U24.28 (VDD1_1)
unnamed: C287.2, C288.1, U24.2 (VDD2_0)
unnamed: C295.2, C296.1, U24.29 (VDD2_1)
unnamed: C288.2, C290.1, U24.1 (VDD3_0)
unnamed: C293.2, C295.1, U24.30 (VDD3_1)
unnamed: R76.1, U25.11 (LITE_PAD)
unnamed: C302.2, C303.1, U25.3 (VDD1_0)
unnamed: C312.2, C315.1, U25.28 (VDD1_1)
unnamed: C303.2, C304.1, U25.2 (VDD2_0)
unnamed: C311.2, C312.1, U25.29 (VDD2_1)
unnamed: C304.2, C306.1, U25.1 (VDD3_0)
unnamed: C309.2, C311.1, U25.30 (VDD3_1)
unnamed: R78.1, U26.11 (LITE_PAD)
unnamed: C318.2, C319.1, U26.3 (VDD1_0)
unnamed: C328.2, C331.1, U26.28 (VDD1_1)
unnamed: C319.2, C320.1, U26.2 (VDD2_0)
unnamed: C327.2, C328.1, U26.29 (VDD2_1)
unnamed: C320.2, C322.1, U26.1 (VDD3_0)
unnamed: C325.2, C327.1, U26.30 (VDD3_1)
unnamed: R80.1, U27.11 (LITE_PAD)
unnamed: C334.2, C335.1, U27.3 (VDD1_0)
unnamed: C344.2, C347.1, U27.28 (VDD1_1)
unnamed: C335.2, C336.1, U27.2 (VDD2_0)
unnamed: C343.2, C344.1, U27.29 (VDD2_1)
unnamed: C336.2, C338.1, U27.1 (VDD3_0)
unnamed: C341.2, C343.1, U27.30 (VDD3_1)
unnamed: R82.1, U28.11 (LITE_PAD)
unnamed: C350.2, C351.1, U28.3 (VDD1_0)
unnamed: C360.2, C363.1, U28.28 (VDD1_1)
unnamed: C351.2, C352.1, U28.2 (VDD2_0)
unnamed: C359.2, C360.1, U28.29 (VDD2_1)
unnamed: C352.2, C354.1, U28.1 (VDD3_0)
unnamed: C357.2, C359.1, U28.30 (VDD3_1)
unnamed: R85.1, U29.4 (ADDR_SEL)
unnamed: R86.1, U29.11 (CLK)
unnamed: R100.1, TP18.1, U30.2 (CLK), U31.62 (EECLK)
unnamed: R98.1, TP19.1, U30.1 (CS), U31.63 (EECS)
unnamed: R96.2, TP17.1, U30.3 (D), U31.61 (EEDATA)
unnamed: R95.1, R96.1, U30.4 (Q)
unnamed: C365.1, U31.2 (OSCI), Y2.1
unnamed: C368.1, U31.3 (OSCO), Y2.3
unnamed: R101.2, TP20.1, U31.6 (REF)
unnamed: R102.2, U31.14 (RESET#)
unnamed: C366.1, C371.1, FB1.2, U31.4 (VPHY)
unnamed: C367.1, C369.1, FB2.2, U31.9 (VPLL)
VDD: C59.1, C60.1, C61.1, C62.1, C63.1, C64.1, C65.1, C66.1, C67.1, C68.1, C69.1, C70.1, C71.1, C72.1, C73.1, C74.1, C75.1, C76.1, C77.1, C78.1, C79.1, C80.1, C81.1, C82.1, C83.1, C84.1, C85.1, C86.1, C87.1, C88.1, C89.1, C90.1, C91.1, C92.1, C93.1, C94.1, C95.1, C96.1, C97.1, C98.1, C99.1, C100.1, C101.1, C102.1, C103.1, C104.1, C105.1, C106.1, C107.1, C108.1, C177.1, C178.2, C179.1, C180.1, C181.1, C182.1, C193.1, C194.2, C195.1, C196.1, C197.1, C198.1, C209.1, C210.2, C211.1, C212.1, C213.1, C214.1, C225.1, C226.2, C227.1, C228.1, C229.1, C230.1, C241.1, C242.2, C243.1, C244.1, C245.1, C246.1, C257.1, C258.2, C259.1, C260.1, C261.1, C262.1, C273.1, C274.2, C275.1, C276.1, C277.1, C278.1, C289.1, C290.2, C291.1, C292.1, C293.1, C294.1, C305.1, C306.2, C307.1, C308.1, C309.1, C310.1, C321.1, C322.2, C323.1, C324.1, C325.1, C326.1, C337.1, C338.2, C339.1, C340.1, C341.1, C342.1, C353.1, C354.2, C355.1, C356.1, C357.1, C358.1, L3.2, L4.2, L5.2, L6.2, L7.2, L8.2, NT1.1, U17.31 (VDD), U18.31 (VDD), U19.31 (VDD), U20.31 (VDD), U21.31 (VDD), U22.31 (VDD), U23.31 (VDD), U24.31 (VDD), U25.31 (VDD), U26.31 (VDD), U27.31 (VDD), U28.31 (VDD)

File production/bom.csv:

Designator,Footprint,Quantity,Value,LCSC Part #
C1,0603,1,10uF,
"C10, C11, C12, C13, C14, C16, C17, C18, C19, C23, C24, C27, C3, C4, C5, C6, C7, C8, C9",0402,19,100nF,
"C100, C101, C102, C103, C104, C105, C106, C107, C108, C59, C62, C65, C66, C69, C72, C73, C76, C77, C80, C81, C84, C85, C88, C89, C92, C93, C96, C97, C98, C99",1210,30,330µF/4V,
"C109, C117, C127, C137, C147, C157, C38, C39, C41, C42, C43, C44, C45, C46, C47, C48, C49, C50, C53",1210,19,22µ/25V,
"C110, C118, C128, C138, C148, C158, C169, C171, C180, C196, C212, C228, C244, C260, C276, C292, C308, C324, C340, C356, C52, C54",0805,22,1µF/25V,
"C111, C116, C119, C124, C129, C134, C139, C144, C149, C154, C159, C164, C36, C37, C58",0805,15,1nF,
"C112, C113, C115, C120, C121, C123, C130, C131, C133, C140, C141, C143, C150, C151, C153, C160, C161, C163, C165, C166, C167, C168, C170, C182, C198, C214, C230, C246, C262, C278, C294, C310, C326, C342, C358",0805,35,100nF,
"C114, C122, C132, C142, C152, C162",0805,6,2.2µF/16V,
"C125, C126, C135, C136, C145, C146, C155, C156",0603,8,100n,
"C15, C2",0402,2,10uF,
"C172, C173, C174, C175, C176, C178, C181, C183, C184, C185, C186, C187, C188, C189, C190, C191, C192, C194, C197, C199, C200, C201, C202, C203, C204, C205, C206, C207, C208, C210, C213, C215, C216, C217, C218, C219, C220, C221, C222, C223, C224, C226, C229, C231, C232, C233, C234, C235, C236, C237, C238, C239, C240, C242, C245, C247, C248, C249, C250, C251, C252, C253, C254, C255, C256, C258, C261, C263, C264, C265, C266, C267, C268, C269, C270, C271, C272, C274, C277, C279, C280, C281, C282, C283, C284, C285, C286, C287, C288, C290, C293, C295, C296, C297, C298, C299, C300, C301, C302, C303, C304, C306, C309, C311, C312, C313, C314, C315, C316, C317, C318, C319, C320, C322, C325, C327, C328, C329, C330, C331, C332, C333, C334, C335, C336, C338, C341, C343, C344, C345, C346, C347, C348, C349, C350, C351, C352, C354, C357, C359, C360, C361, C362, C363",0603,144,1µF/6.3V,
"C177, C193, C209, C225, C241, C257, C273, C289, C305, C31, C321, C337, C353",0805,13,10µF/25V,
"C179, C195, C211, C227, C243, C259, C275, C291, C307, C323, C339, C355, C60, C61, C63, C64, C67, C68, C70, C71, C74, C75, C78, C79, C82, C83, C86, C87, C90, C91, C94, C95",1206,32,100µ/6.3V,
C20,0402,1,10pF,
C21,0402,1,1uF,
C22,0603,1,22uF,
"C25, C26",0402,2,18pF,
"C28, C29, C30, C32",CP_Elec_8x10,4,470µ/25V,
"C33, C35",0805,2,22pF,
C34,0805,1,100pF,
"C364, C369, C371, C372, C373, C374, C375, C376, C377, C378",0805,10,0.1uF,C28233
"C365, C368",0805,2,27pf,C107113
"C366, C367",0805,2,4.7uF,C1746
C370,0805,1,3.3uF,C159781
C40,0805,1,10nF,
C51,0805,1,4.7µF/16V,
C55,0805,1,330nF,
C56,0805,1,12pF,
C57,0805,1,2.2nF,
D1,D_SOD-128,1,"PMEG4030EP,115",
"FB1, FB2",0603,2,FerriteBead_Small,C19330
J1,PCIexpress_bracket_full,1,PCIexpress_bracket,
"J10, J7, J8, J9",CONN-TH_4P-P2.54_HCTL_HC-2510-4AW,4,61900411021,C2982043
J2,PCIexpress_x4,1,PCIexpress_x4,
"J3, J4, J5",MOLEX_353180620,3,353180620,
L1,L_Vishay_IHLP-1212,1,1uH,
L2,L_Taiyo-Yuden_NR-50xx,1,4.7µH,
"L3, L4, L5, L6, L7, L8",IFLR-4031GC-01-8x10,6,220nH,
"R1, R13, R14, R2, R30, R31, R34, R35",0603,8,49.9,
R10,0402,1,6.04K,
"R100, R91, R92, R93, R94, R95, R98",0805,7,10k,C17414
R101,0805,1,12k,C17444
R102,0805,1,1k,C17513
R11,0402,1,15K,
"R12, R5, R6, R8",0402,4,10K,
"R15, R23",0805,2,16.5K,
R16,0805,1,24.3K,
"R17, R18",0805,2,51 0.5%,
R19,0805,1,121K,
"R20, R21, R46, R47, R48",0805,5,10K,
R22,0805,1,86.6K,
R24,0805,1,2.55K,
R25,0805,1,8.06K,
R26,0805,1,49.9K,
R27,0805,1,100K,
"R28, R29",0805,2,2.2R,
R3,0402,1,75K,
"R32, R33, R36, R37, R38, R39, R40, R41, R42, R43, R44, R45",0805,12,1R,
R4,0402,1,100K,
"R49, R50, R51, R52, R53, R54, R55, R56, R57, R58, R59",0402,11,33R,
"R60, R62, R64, R66, R68, R70, R72, R74, R76, R78, R80, R82",0805,12,1K,
"R61, R63, R65, R67, R69, R71, R73, R75, R77, R79, R81, R83",0805,12,2K,
R7,0402,1,DNP,
"R84, R97, R99",0805,3,4.7k,C17673
R85,0805,1,33k,C17633
R86,0805,1,22k,C17560
"R87, R88, R89, R90",0805,4,36k,C114527
R9,0402,1,4.7K,
R96,0805,1,2.2k,C17520
"TP1, TP10, TP11, TP12, TP13, TP14, TP15, TP16, TP2, TP3, TP4, TP5, TP6, TP7, TP8, TP9",TestPoint_Pad_D1.0mm,16,TestPoint,
U1,SOT-563,1,TLV62568ADRLR,
"U10, U11, U12, U7, U8, U9",IC_CSD95490Q5MC,6,CSD95472Q5MC,
U13,Oscillator_SMD_EuroQuartz_XO32-4Pin_3.2x2.5mm,1,25MHz,
U14,TSSOP-14-1EP_4.4x5mm_P0.65mm,1,TXU0304PW,
U15,SOT-23-5,1,MCP1824T-0802E,
U16,SOT-23-5,1,MCP1824T-1202E,
"U17, U18, U19, U20, U21, U22, U23, U24, U25, U26, U27, U28",BM1370,12,BM1370_mode1,
U2,SOT-23-5,1,AP2204K-1.8,
U29,QFN16_4x4MC_MCH,1,EMC2305,
U3,QFN-68-1EP_8x8mm_P0.4mm_EP5.2x5.2mm,1,VL805,
U30,TSSOP-8_L4.4-W3.0-P0.65-LS6.4-BL,1,M93C46-WDW6TP,C616741
U31,QFN50P900X900X105-65N,1,FT4232HQ,C2651882
U4,DFN-8-1EP_3x2mm_P0.5mm_EP1.36x1.46mm,1,W25Q32JVZP,
U5,SOT-23-6,1,AP3211,
U6,IC_TPS53667RTAR,1,TPS53667RTAR,
Y1,Crystal_SMD_3225-4Pin_3.2x2.5mm,1,25Mhz,
Y2,Crystal_SMD_3225-4Pin_3.2x2.5mm,1,12MHz,C251626

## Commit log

2025-07-02 Initial commit: Added KiCad project files
2025-07-02 Added 3D render images and updated README
2025-07-11 Update README.md
    Copyrights updated
2025-07-11 Update LICENSE
2025-07-11 Remove MIT license for relicensing
2025-07-11 Add .gitignore to exclude backup zips
2025-07-11 Relicense to TAPR OHL-NC
2025-07-11 Add TAPR OHL-NC license badge to README
2025-07-11 Update README.md
    coppyrights updated
2025-07-25 board stakup updated and schematic is updated
2025-11-02 updated schematic working on layout
2025-12-06 Updated new layout and routing of PCB
2025-12-06 Removed backup files from tracking and updated .gitignore
2026-02-23 Project cleanup and update
2026-03-04 Updated after DRC
2026-03-04 Updated PCB images

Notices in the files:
README.md:
License: TAPR OHL-NC
